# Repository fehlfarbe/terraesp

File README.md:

# ESP32 terrarium controller

With this project you can control your terrarium's temperature, light, sprinkler and so on via webinterface.

## Features

* Reads different Sensors for temperature and humidity (DHT22, SHT3x, DS1820, ...) and analog sensors to measure soil moisture etc.
* Timers for day/night light switch
* Actions if threshold for a sensor is reached e.g. to start sprinkler for 10s if humidity is under threshold
* Webinterface:
  * 24h log of temperature and humidity, actions etc.
  * control for buttons/actors and sliders for PWM pins
  * change config
* OTA update via WiFi

## Webinterface

The webinterface has interactive controls to toggle relays or set PWM values to set the brightness of LEDs or fan speed.

A chart shows the measured temperatures (red) and humidity (blue) of your configured sensors and events (green) like time on, off and so on.

You can add sensors, actuators (relay, pwm), timers and thresholds in the 'settings' section.

## Parts needed

* ESP32 dev board
* DHT22 / SHT31 / analog temperature and humidity sensor
* Relay or SSR board to control lights/pump
* MOSFET board to control LED brightness, fan speed etc. via PWM
* WiFi connection for time sync

The device creates an access point on first start. Then you can configure your WiFi and pin settings.

## Caution

The WiFi password is saved without encryption on the device. Also OTA-update has default password "admin" at the moment. Change it if you want to secure your device for unauthorized updates.

> **Make the webinterface accessible from the internet is a very bad idea! Please use a VPN or something else to prevent a flooded terrarium ;-)**

## Installation

* Download / Clone this repository
* Install PlatformIO: <https://docs.platformio.org/en/latest/ide/pioide.html>
* Open this project in PlatformIO
* Connect your ESP32 via USB cable and upload sketch and [filesystem](https://docs.platformio.org/en/latest/platforms/espressif32.html#uploading-files-to-file-system-spiffs)
  * Run task -> Upload file system image
  * or run `pio run -t uploadfs`
  * Uploading filesystem will overwrite your settings!
* Reboot ESP32, it will create an AccessPoint with name ESP_xxxx
* Connect to the AP and open <http://192.168.4.1> in Browser
* Connect to your WiFi network
* Setup pins, sensor and so on in the webinterface

## Problems

* If PlatformIO can't find the libraries, switch to the cloned directory, open a terminal and type `pio lib install`. The command should download all necessary libraries.
* Windows users: if you get errors like `error: 'timeinfo' has incomplete type` just delete the `Time.h` header in `.pio/libdeps/{ota,usb}/Time` after installing the libs. The bug happens only on Windows because it's not case-sensitive and mixes the `time.h` header with `Time.h` of TimeLib library.

## PCB

Prototype PCB with several new features:

* 12V supply voltage for board and PWM/switches
* Directly soldered ESP32 with 12V -> 5V -> 3V3 converter
* 4x SSR to switch 230V AC with one 230V AC input and 3-4x outputs (is this safe??)
* 4x MOSFETs for PWM with supply voltage (to set the brightness of a 12V LED strip or control the speed of a fan)
* Connect multiple sensors/displays/whatever via i2c bus
* Connect analog sensors

## ToDo

* [ ] webinterface with authorization
* [ ] better instructions
* [ ] import/export config
* [x] The current hardware setup is a mess  with many jumper cables and so on. So I want to create PCB with relays/SSR, MOSFETS, power supply
* [ ] PID controller for heater/humidifier?
* [ ] PCB: switch from EAGLE to KiCAD (in progress...)
* [ ] PCB: replace the expensive 12V -> 5V step down (in progress...)

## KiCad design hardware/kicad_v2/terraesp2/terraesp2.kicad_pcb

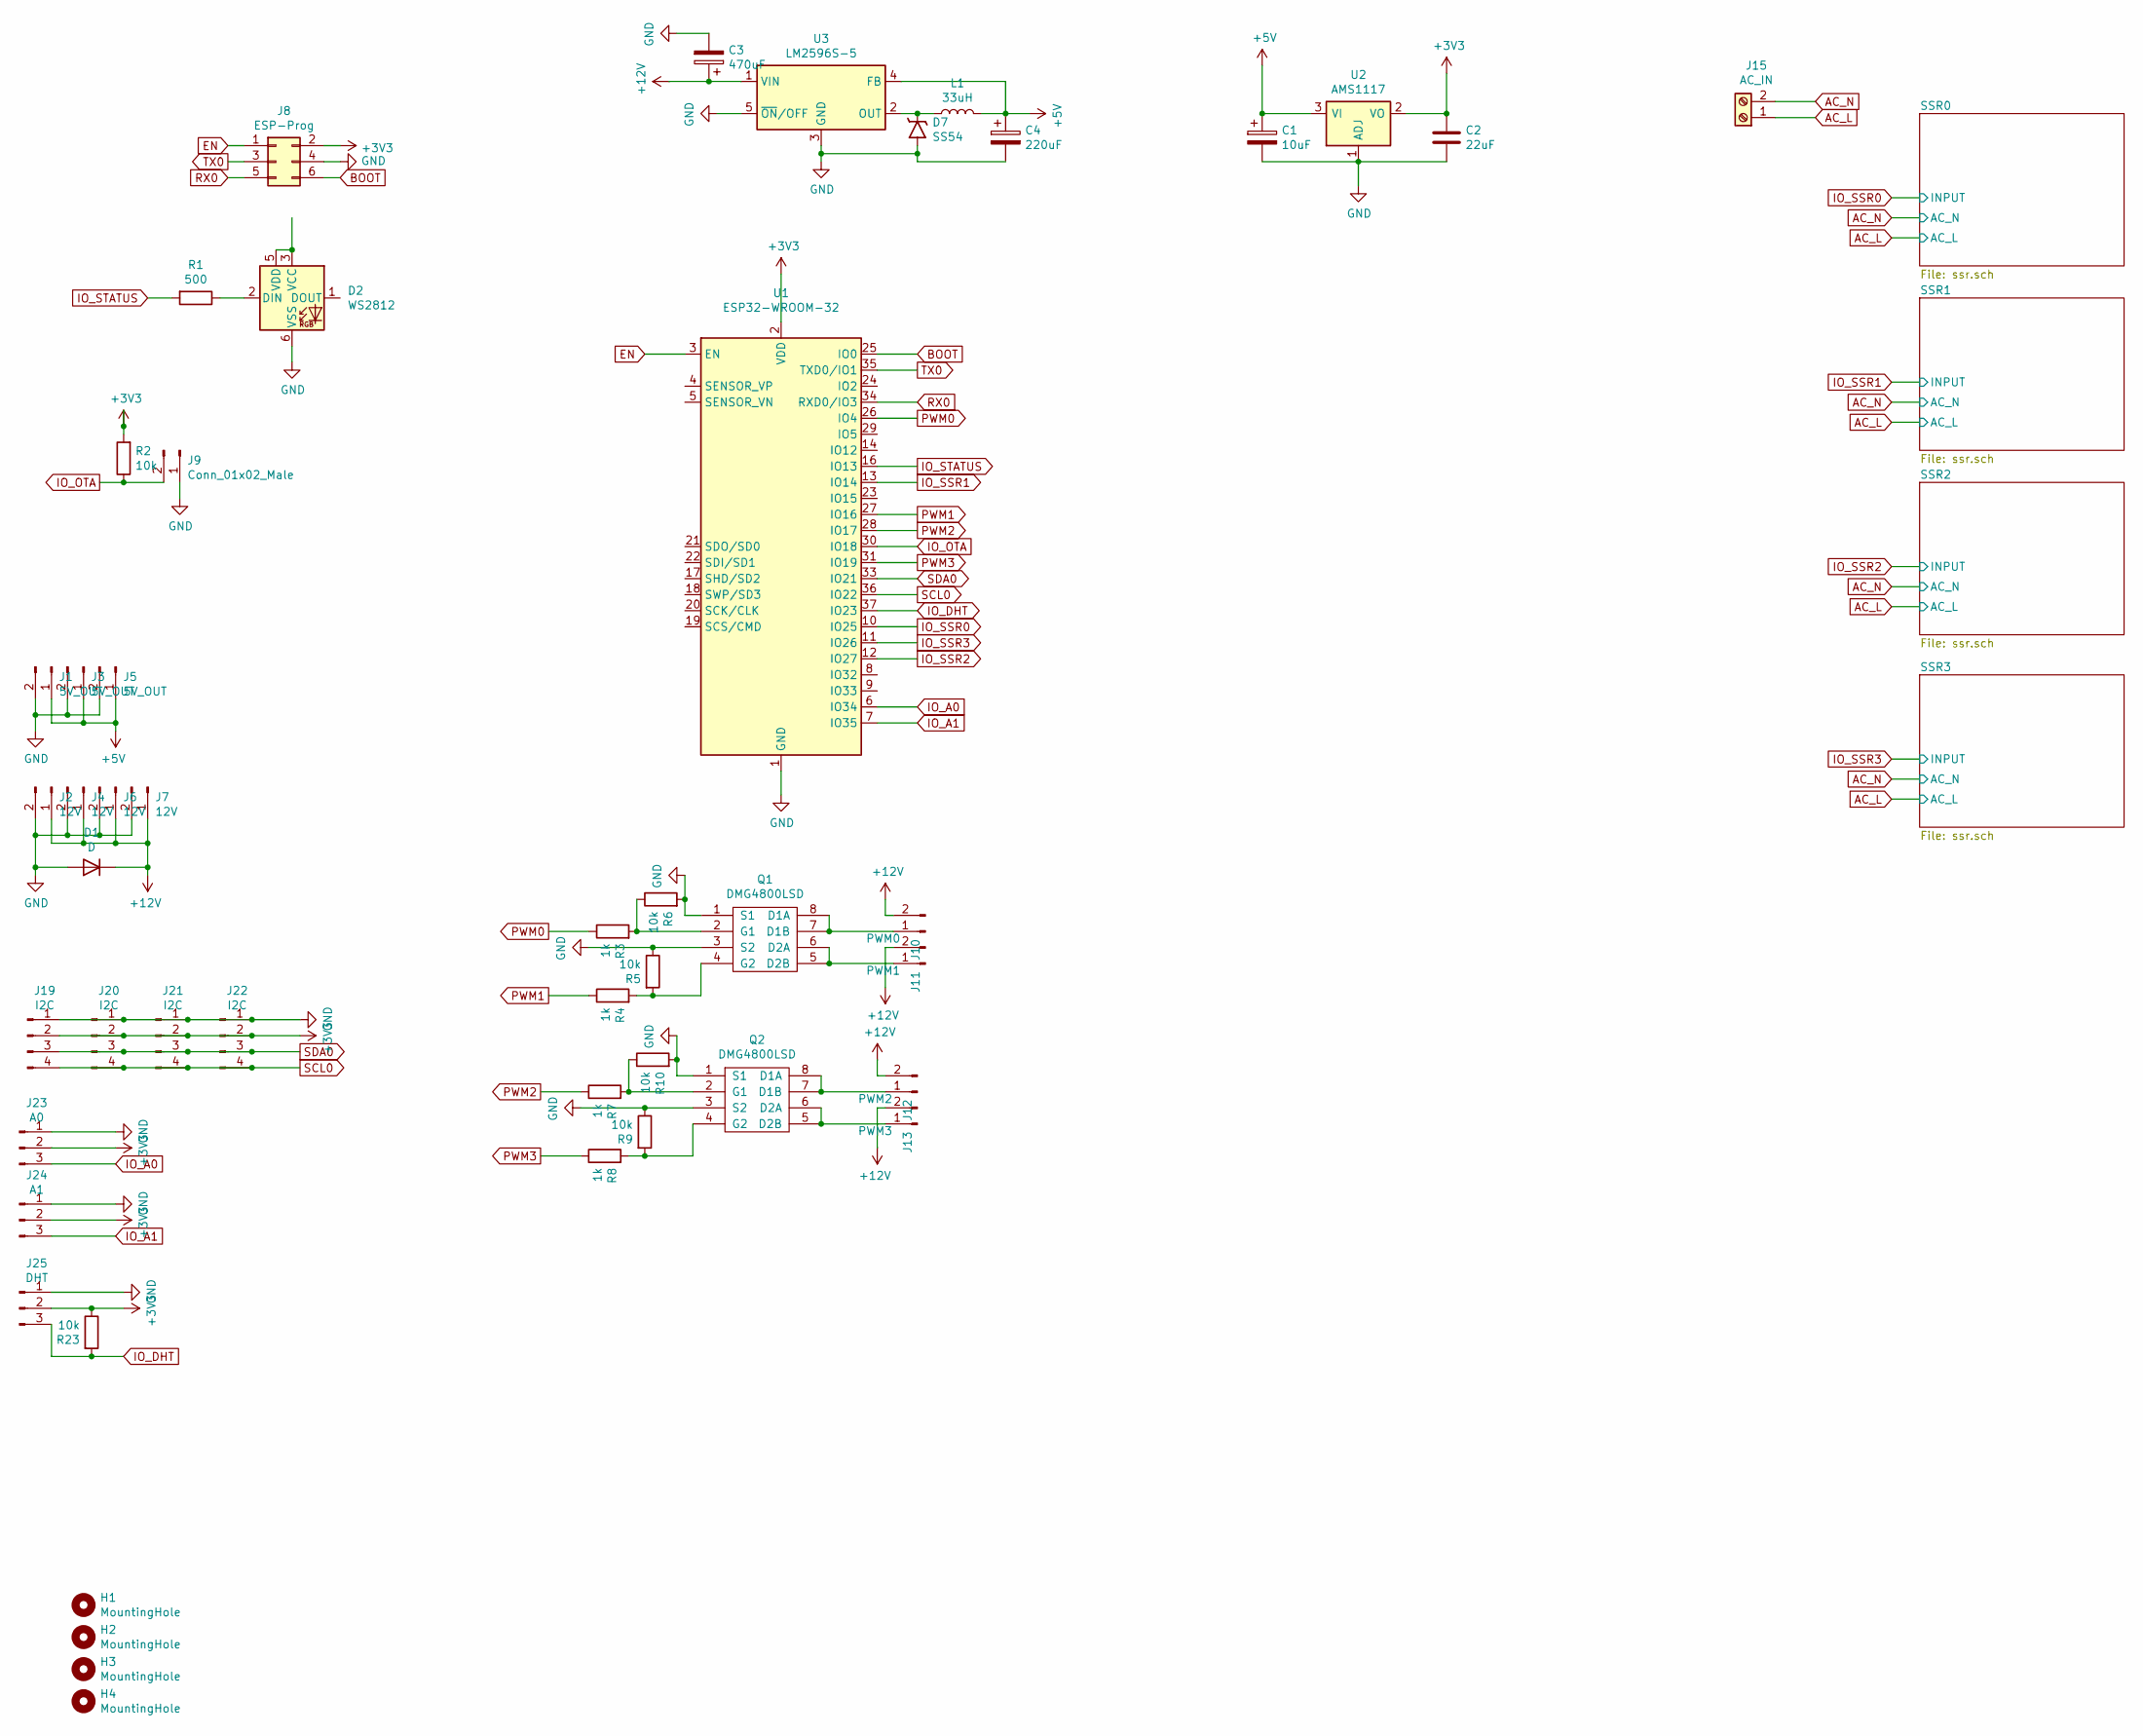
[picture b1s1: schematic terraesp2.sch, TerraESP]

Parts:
C1: 10uF; C_1206_3216Metric
C2: 22uF; CP_EIA-1608-08_AVX-J
C3: 470uF; CP_Elec_10x10.5
C4: 220uF; CP_Elec_6.3x5.8
D1: D; D_1206_3216Metric
D2: WS2812; LED_WS2812_PLCC6_5.0x5.0mm_P1.6mm
D7: SS54; DO-214AC
H1, H2, H3, H4: MountingHole; MountingHole_3.2mm_M3
J1, J3, J5: 5V_OUT; Molex_KK-254_AE-6410-02A_1x02_P2.54mm_Vertical
J2, J4, J6, J7: 12V; Molex_KK-254_AE-6410-02A_1x02_P2.54mm_Vertical
J8: ESP-Prog; IDC-Header_2x03_P2.54mm_Vertical
J9: Conn_01x02_Male; PinHeader_1x02_P2.54mm_Vertical
J10: PWM0; Molex_KK-254_AE-6410-02A_1x02_P2.54mm_Vertical
J11: PWM1; Molex_KK-254_AE-6410-02A_1x02_P2.54mm_Vertical
J12: PWM2; Molex_KK-254_AE-6410-02A_1x02_P2.54mm_Vertical
J13: PWM3; Molex_KK-254_AE-6410-02A_1x02_P2.54mm_Vertical
J15: AC_IN; TerminalBlock_Phoenix_MKDS-1,5-2_1x02_P5.00mm_Horizontal
J19, J20, J21, J22: I2C; Molex_KK-254_AE-6410-04A_1x04_P2.54mm_Vertical
J23: A0; Molex_KK-254_AE-6410-03A_1x03_P2.54mm_Vertical
J24: A1; Molex_KK-254_AE-6410-03A_1x03_P2.54mm_Vertical
J25: DHT; Molex_KK-254_AE-6410-03A_1x03_P2.54mm_Vertical
L1: 33uH; L_12x12mm_H8mm
Q1, Q2: DMG4800LSD; Diodes_Inc.-SO-8-03_2017-0-MFG
R1: 500; R_1206_3216Metric
R2, R5, R6, R9, R10, R23: 10k; R_1206_3216Metric
R3, R4, R7, R8: 1k; R_1206_3216Metric
U1: ESP32-WROOM-32
U2: AMS1117; SOT-223-3_TabPin2
U3: LM2596S-5; TO-263-5_TabPin3

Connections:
+3V3: C2.1, J8.2, J19.2, J20.2, J21.2, J22.2, J23.2, J24.2, J25.2, R2.2, R23.1, U1.2 (VDD), U2.2 (VO)
+5V: C1.1, C4.1, J1.1, J3.1, J5.1, L1.2, U2.3 (VI), U3.4 (FB); also elsewhere on the board
+12V: C3.1, D1.1 (K), J2.1, J4.1, J6.1, J7.1, J10.2, J11.2, J12.2, J13.2, U3.1 (VIN)
AC_L: J15.1; also elsewhere on the board
AC_N: J15.2; also elsewhere on the board
BOOT: J8.6, U1.25 (IO0)
EN: J8.1, U1.3 (EN)
GND: C1.2, C2.2, C3.2, C4.2, D1.2 (A), D2.6 (VSS), D7.A, J1.2, J2.2, J3.2, J4.2, J5.2, J6.2, J7.2, J8.4, J9.1, J19.1, J20.1, J21.1, J22.1, J23.1, J24.1, J25.1, Q1.1 (S1), Q1.3 (S2), Q2.1 (S1), Q2.3 (S2), R5.1, R6.2, R9.1, R10.2, U1.1 (GND), U1.15 (GND), U1.38 (GND), U1.39 (GND), U2.1 (ADJ), U3.3 (GND), U3.5 (~ON~/OFF); also elsewhere on the board
IO_A0: J23.3, U1.6 (IO34)
IO_A1: J24.3, U1.7 (IO35)
IO_DHT: J25.3, R23.2, U1.37 (IO23)
IO_OTA: J9.2, R2.1, U1.30 (IO18)
IO_SSR0: U1.10 (IO25); also elsewhere on the board
IO_SSR1: U1.13 (IO14); also elsewhere on the board
IO_SSR2: U1.12 (IO27); also elsewhere on the board
IO_SSR3: U1.11 (IO26); also elsewhere on the board
IO_STATUS: R1.2, U1.16 (IO13)
unnamed: D2.2 (DIN), R1.1
unnamed: D2.3 (VCC), D2.5 (VDD)
unnamed: D7.C, L1.1, U3.2 (OUT)
unnamed: J10.1, Q1.7 (D1B), Q1.8 (D1A)
unnamed: J11.1, Q1.5 (D2B), Q1.6 (D2A)
unnamed: J12.1, Q2.7 (D1B), Q2.8 (D1A)
unnamed: J13.1, Q2.5 (D2B), Q2.6 (D2A)
unnamed: Q1.2 (G1), R3.2, R6.1
unnamed: Q1.4 (G2), R4.2, R5.2
unnamed: Q2.2 (G1), R7.2, R10.1
unnamed: Q2.4 (G2), R8.2, R9.2
PWM0: R3.1, U1.26 (IO4)
PWM1: R4.1, U1.27 (IO16)
PWM2: R7.1, U1.28 (IO17)
PWM3: R8.1, U1.31 (IO19)
RX0: J8.5, U1.34 (RXD0/IO3)
SCL0: J19.4, J20.4, J21.4, J22.4, U1.36 (IO22)
SDA0: J19.3, J20.3, J21.3, J22.3, U1.33 (IO21)
TX0: J8.3, U1.35 (TXD0/IO1)

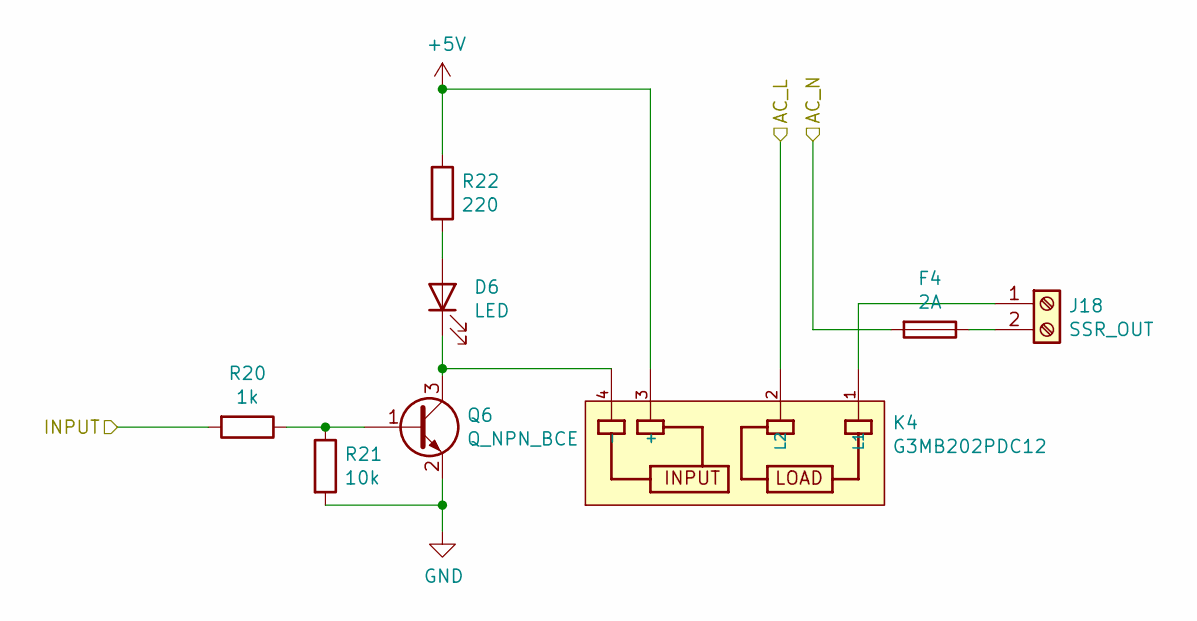
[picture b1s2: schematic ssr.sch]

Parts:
D3: LED; LED_1206_3216Metric
F1: 2A; ASI PTF-76 5x20mm Fuse Holder
J14: SSR_OUT; TerminalBlock_Phoenix_MKDS-1,5-2_1x02_P5.00mm_Horizontal
K1: G3MB202PDC12; RELAY_G3MB202PDC12; PARTREV N/A
Q3: Q_NPN_BCE; SOT-23
R11: 1k; R_1206_3216Metric
R12: 10k; R_1206_3216Metric
R13: 220; R_1206_3216Metric

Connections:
+5V: K1.3 (+), R13.1; also elsewhere on the board
AC_L: K1.2 (L2); also elsewhere on the board
AC_N: F1.2; also elsewhere on the board
GND: Q3.2 (E), R12.2; also elsewhere on the board
IO_SSR0: R11.2; also elsewhere on the board
unnamed: D3.1 (K), K1.4 (-), Q3.3 (C)
unnamed: D3.2 (A), R13.2
unnamed: F1.1, J14.2
unnamed: J14.1, K1.1 (L1)
unnamed: Q3.1 (B), R11.1, R12.1

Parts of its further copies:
D4, D5, D6: LED; LED_1206_3216Metric
F2, F3, F4: 2A; ASI PTF-76 5x20mm Fuse Holder
J16, J17, J18: SSR_OUT; TerminalBlock_Phoenix_MKDS-1,5-2_1x02_P5.00mm_Horizontal
K2, K3, K4: G3MB202PDC12; RELAY_G3MB202PDC12; PARTREV N/A
Q4, Q5, Q6: Q_NPN_BCE; SOT-23
R14, R17, R20: 1k; R_1206_3216Metric
R15, R18, R21: 10k; R_1206_3216Metric
R16, R19, R22: 220; R_1206_3216Metric

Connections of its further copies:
+5V: K2.3 (+), K3.3 (+), K4.3 (+), R16.1, R19.1, R22.1; also elsewhere on the board
AC_L: K2.2 (L2), K3.2 (L2), K4.2 (L2); also elsewhere on the board
AC_N: F2.2, F3.2, F4.2; also elsewhere on the board
GND: Q4.2 (E), Q5.2 (E), Q6.2 (E), R15.2, R18.2, R21.2; also elsewhere on the board
IO_SSR1: R14.2; also elsewhere on the board
IO_SSR2: R17.2; also elsewhere on the board
IO_SSR3: R20.2; also elsewhere on the board
unnamed: D4.1 (K), K2.4 (-), Q4.3 (C)
unnamed: D4.2 (A), R16.2
unnamed: D5.1 (K), K3.4 (-), Q5.3 (C)
unnamed: D5.2 (A), R19.2
unnamed: D6.1 (K), K4.4 (-), Q6.3 (C)
unnamed: D6.2 (A), R22.2
unnamed: F2.1, J16.2
unnamed: F3.1, J17.2
unnamed: F4.1, J18.2
unnamed: J16.1, K2.1 (L1)
unnamed: J17.1, K3.1 (L1)
unnamed: J18.1, K4.1 (L1)
unnamed: Q4.1 (B), R14.1, R15.1
unnamed: Q5.1 (B), R17.1, R18.1
unnamed: Q6.1 (B), R20.1, R21.1

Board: 2 copper layers, 81 parts (0 on the bottom side), 56 nets, no tracks yet.

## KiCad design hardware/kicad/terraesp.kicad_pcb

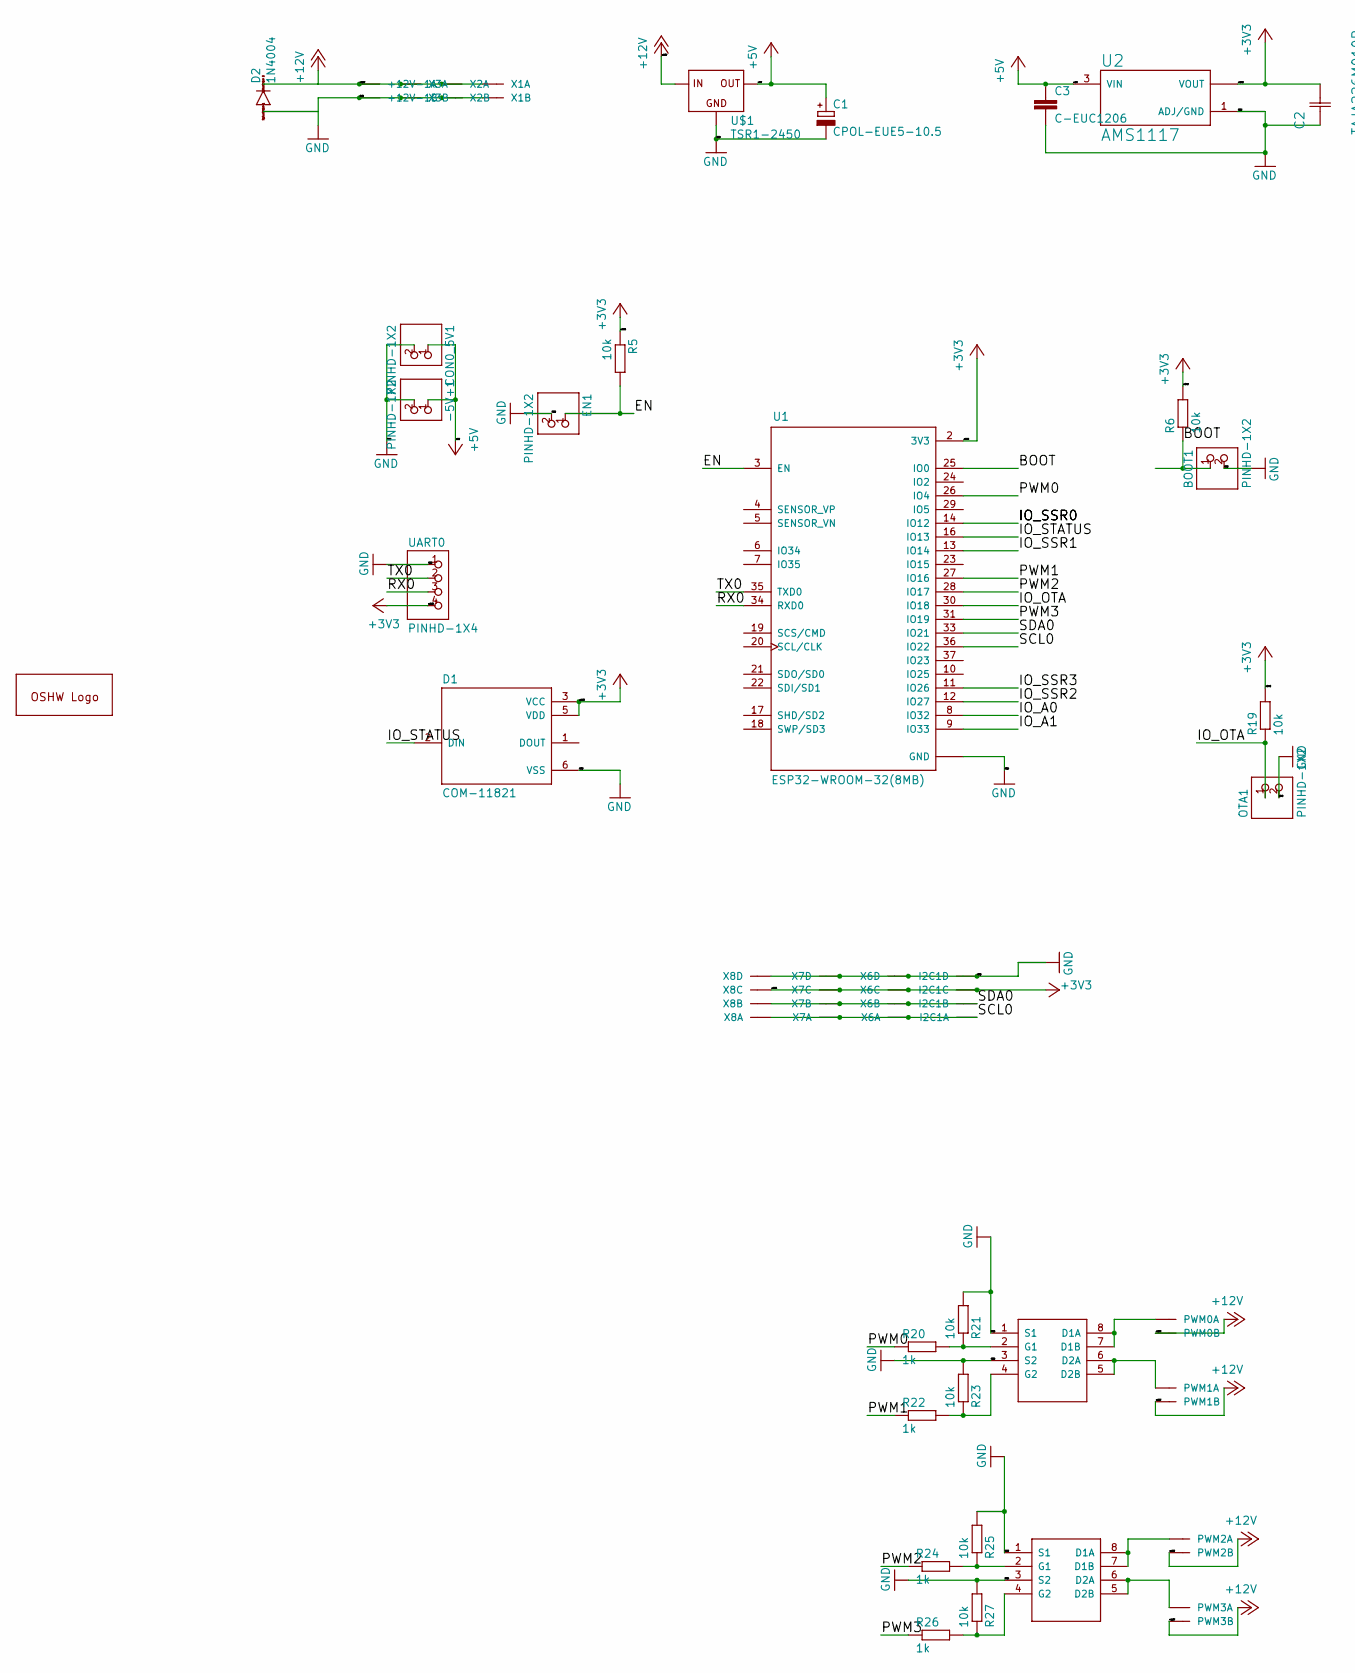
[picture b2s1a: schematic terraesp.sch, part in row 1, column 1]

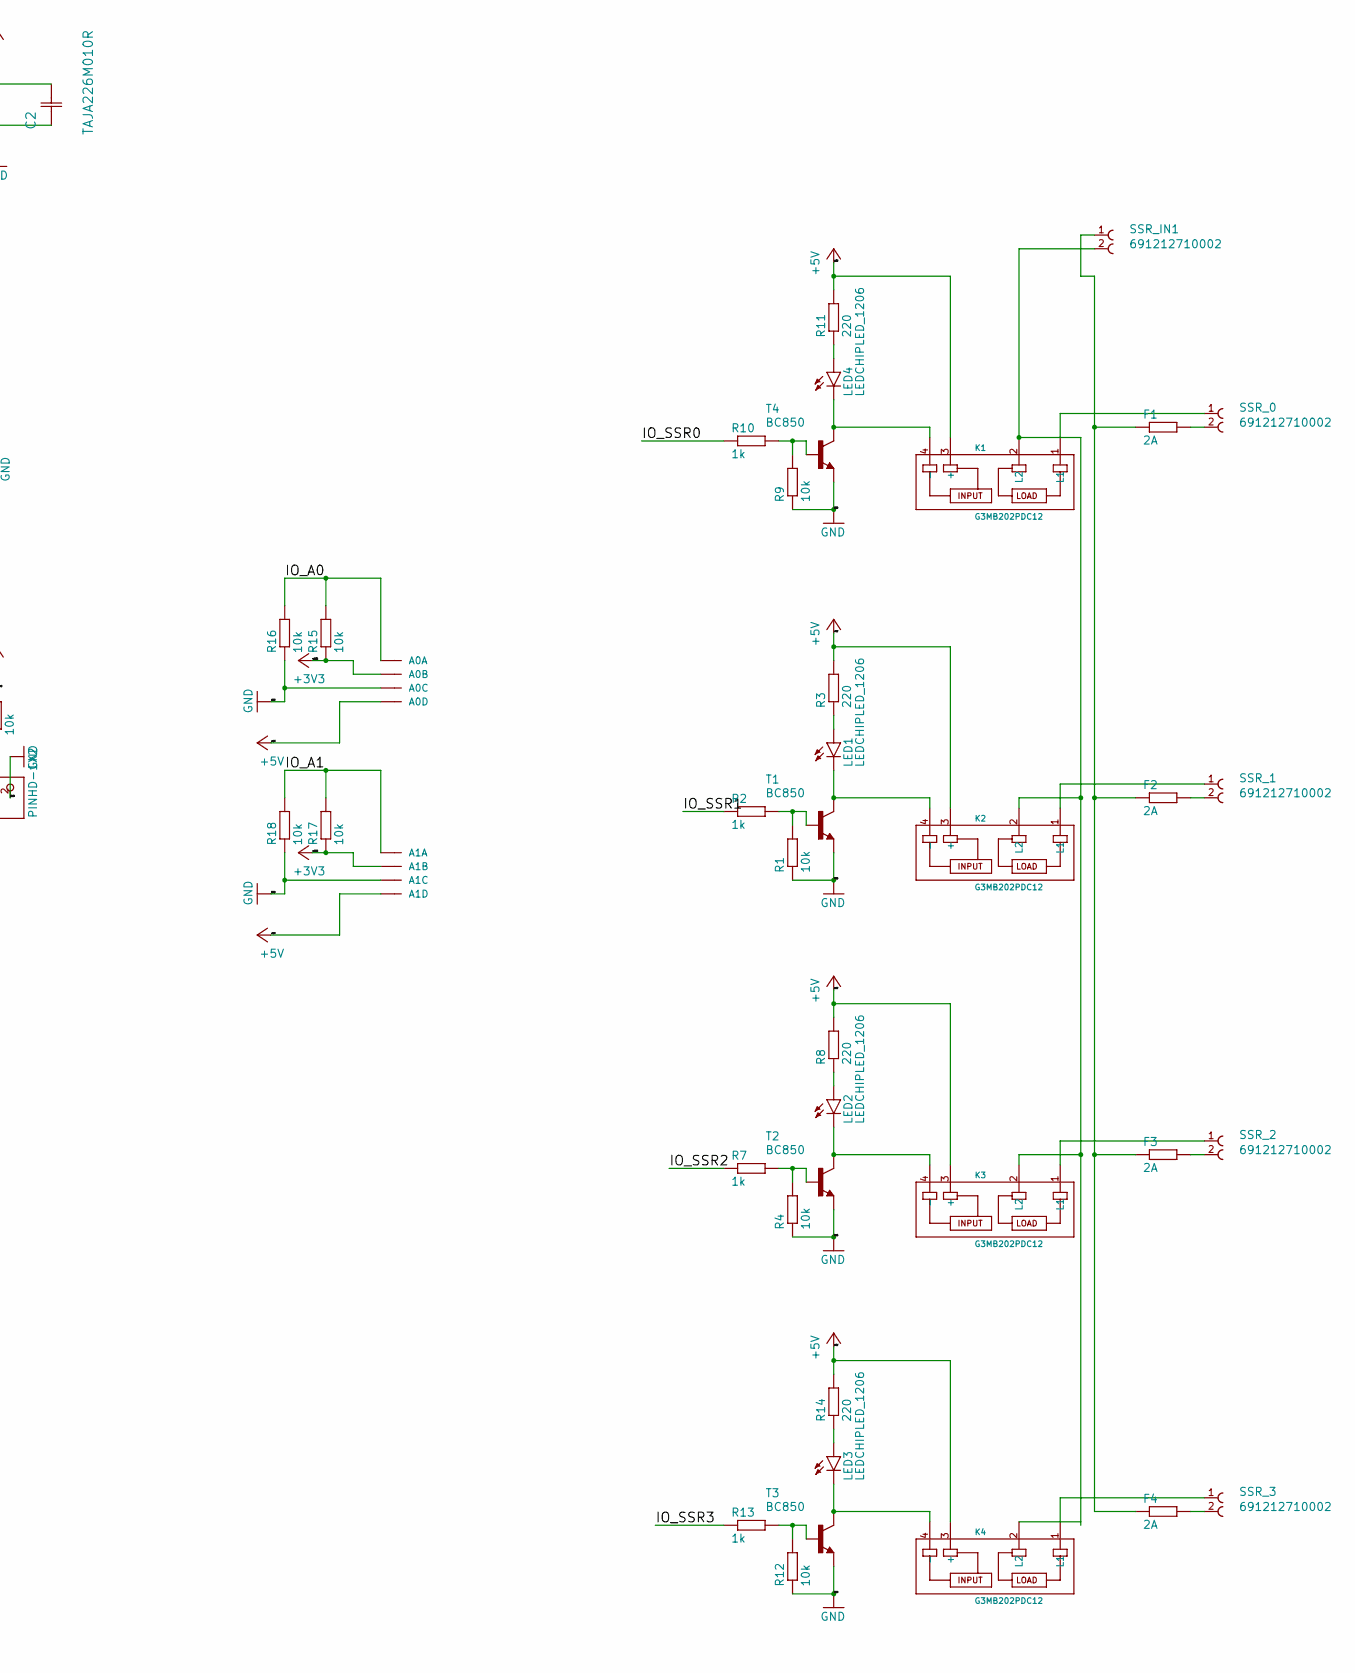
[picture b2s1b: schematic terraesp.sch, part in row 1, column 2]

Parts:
+12V-1: 22-23-2021
-5V+1: PINHD-1X2; 1X02
A0, A1: 22-23-2041
BOOT1: PINHD-1X2; 1X02
C1: CPOL-EUE5-10.5; E5-10,5
C2: TAJA226M010R; CAPCP3216X180N
C3: C-EUC1206; C1206
CON0_5V1: PINHD-1X2; 1X02
D1: COM-11821; LED_COM-11821
D2: 1N4004; DO41-10
EN1: PINHD-1X2; 1X02
F1, F2, F3, F4: 2A; 0207_10
GOLD_ORB_SM2: OSHWLOGOLOGO5MM; OSHW_5MM
I2C1: 22-23-2041
K1, K2, K3, K4: G3MB202PDC12; RELAY_G3MB202PDC12
LED1, LED2, LED3, LED4: LEDCHIPLED_1206; CHIPLED_1206
OTA1: PINHD-1X2; 1X02
PWM0, PWM1, PWM2, PWM3: 22-23-2021
R1, R4, R9, R12: 10k; R1206
R2, R7, R10, R13, R20, R22, R24, R26: 1k; R1206
R3, R8, R11, R14: 220; R1206
R5, R6, R15, R16, R17, R18, R19, R21, R23, R25, R27: 10k; M1206
SSR_0, SSR_1, SSR_2, SSR_3: 691212710002
SSR_IN1: 691212710002
T1, T2, T3, T4: BC850; SOT23
U1: ESP32-WROOM-32(8MB); MODULE_ESP32-WROOM-32(8MB)
U2: AMS1117; SOT229P700X180-4N
U$1: TSR1-2450
U$2, U$3: DMG4800LSD; SOIC127P600X144-8
UART0: PINHD-1X4; 1X04
X1, X2, X3: 22-23-2021
X6, X7, X8: 22-23-2041

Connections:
+3V3: A0.2, A1.2, C2.2 (C2), D1.3 (VCC), D1.5 (VDD), I2C1.3, R5.1, R6.2, R15.1, R17.1, R19.2, U1.2 (3V3), U2.2 (VOUT), U2.4 (VOUT), UART0.4, X6.3, X7.3, X8.3
+5V: -5V+1.1, A0.4, A1.4, C1.+, C3.1, CON0_5V1.1, K1.3 (+), K2.3 (+), K3.3 (+), K4.3 (+), R3.2, R8.2, R11.2, R14.2, U2.3 (VIN), U$1.3 (OUT)
+12V: +12V-1.1, D2.C, PWM0.2, PWM1.2, PWM2.2, PWM3.2, U$1.1 (IN), X1.1, X2.1, X3.1
/BOOT: BOOT1.1, R6.1, U1.25 (IO0)
/EN: EN1.1, R5.2, U1.3 (EN)
/IO_A0: A0.1, R15.2, R16.2, U1.8 (IO32)
/IO_A1: A1.1, R17.2, R18.2, U1.9 (IO33)
/IO_OTA: OTA1.1, R19.1, U1.30 (IO18)
/IO_SSR0: R10.1, U1.14 (IO12)
/IO_SSR1: R2.1, U1.13 (IO14)
/IO_SSR2: R7.1, U1.12 (IO27)
/IO_SSR3: R13.1, U1.11 (IO26)
/IO_STATUS: D1.2 (DIN), U1.16 (IO13)
/PWM0: R20.1, U1.26 (IO4)
/PWM1: R22.1, U1.27 (IO16)
/PWM2: R24.1, U1.28 (IO17)
/PWM3: R26.1, U1.31 (IO19)
/RX0: U1.34 (RXD0), UART0.3
/SCL0: I2C1.1, U1.36 (IO22), X6.1, X7.1, X8.1
/SDA0: I2C1.2, U1.33 (IO21), X6.2, X7.2, X8.2
/TX0: U1.35 (TXD0), UART0.2
GND: +12V-1.2, -5V+1.2, A0.3, A1.3, BOOT1.2, C1.-, C2.1 (C1), C3.2, CON0_5V1.2, D1.6 (VSS), EN1.2, I2C1.4, OTA1.2, R1.1, R4.1, R9.1, R12.1, R16.1, R18.1, R21.2, R23.2, R25.2, R27.2, T1.2 (E), T2.2 (E), T3.2 (E), T4.2 (E), U1.1 (GND), U1.15 (GND), U1.38 (GND), U1.39 (GND), U2.1 (ADJ/GND), U$1.2 (GND), U$2.1 (S1), U$2.3 (S2), U$3.1 (S1), U$3.3 (S2), UART0.1, X1.2, X2.2, X3.2, X6.4, X7.4, X8.4
unnamed: F1.1, F2.1, F3.1, F4.1, SSR_IN1.1
unnamed: F1.2, SSR_0.2
unnamed: F2.2, SSR_1.2
unnamed: F3.2, SSR_2.2
unnamed: F4.2, SSR_3.2
unnamed: K1.1 (L1), SSR_0.1
unnamed: K1.2 (L2), K2.2 (L2), K3.2 (L2), K4.2 (L2), SSR_IN1.2
unnamed: K1.4 (-), LED4.C, T4.3 (C)
unnamed: K2.1 (L1), SSR_1.1
unnamed: K2.4 (-), LED1.C, T1.3 (C)
unnamed: K3.1 (L1), SSR_2.1
unnamed: K3.4 (-), LED2.C, T2.3 (C)
unnamed: K4.1 (L1), SSR_3.1
unnamed: K4.4 (-), LED3.C, T3.3 (C)
unnamed: LED1.A, R3.1
unnamed: LED2.A, R8.1
unnamed: LED3.A, R14.1
unnamed: LED4.A, R11.1
unnamed: PWM0.1, U$2.7 (D1B), U$2.8 (D1A)
unnamed: PWM1.1, U$2.5 (D2B), U$2.6 (D2A)
unnamed: PWM2.1, U$3.7 (D1B), U$3.8 (D1A)
unnamed: PWM3.1, U$3.5 (D2B), U$3.6 (D2A)
unnamed: R1.2, R2.2, T1.1 (B)
unnamed: R4.2, R7.2, T2.1 (B)
unnamed: R9.2, R10.2, T4.1 (B)
unnamed: R12.2, R13.2, T3.1 (B)
unnamed: R20.2, R21.1, U$2.2 (G1)
unnamed: R22.2, R23.1, U$2.4 (G2)
unnamed: R24.2, R25.1, U$3.2 (G1)
unnamed: R26.2, R27.1, U$3.4 (G2)

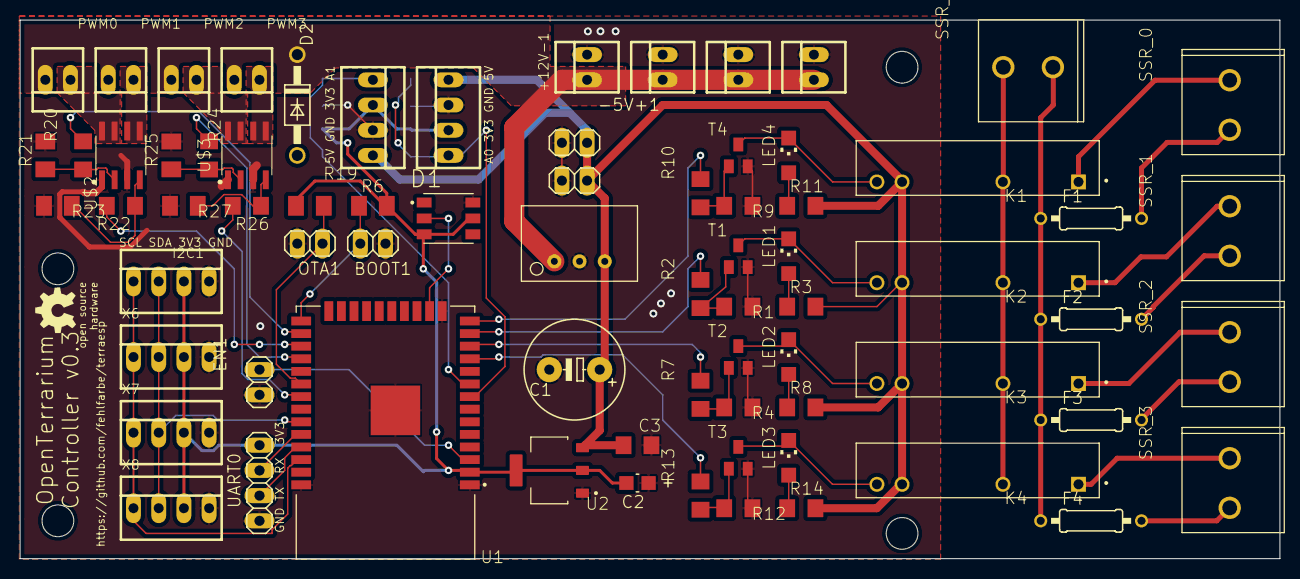
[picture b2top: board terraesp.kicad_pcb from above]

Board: 2 copper layers, 127.0 x 54.3 mm, 83 parts (0 on the bottom side), 52 nets.

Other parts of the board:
@HOLE0, @HOLE1, @HOLE2, @HOLE3: (no value)

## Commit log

2017-10-29 Cleanup
2018-01-03 Added OTA update Device creates Access Point if WiFi network is not reachable (for first config) Fixed some time sync issues Added multiple retries for DHT sensor readout (there are many communicatio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
2018-01-04 Added alternativ DHT library
2018-01-07 Added Serial/Telnet debug output
2018-01-08 Added Serial/Telnet debug output Modified upload.sh - doesn't overwrite config.json on device js librarys are stored local on the device (so internet access is only needed for time update) Some minor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
2018-01-14 Minor fixes
2018-01-21 Added new config menu
2018-01-21 Added some documentation
2019-02-02 converted to platformio
2019-02-10 Changed to platformio project WiFi password is no longer visible on config page
2019-02-10 restructured project
2019-02-12 not working yet
2019-06-09 Added WifiManager, updated platformio.ini and README
2019-09-10 Added new sensors
2019-09-16 Different sensors are working now Reading sensors from config file
2019-09-16 Added prototype PCB layout
2019-10-05 Updated to ArduinoJSON6 Updated Webinterface Compressed CSS/JS files
2019-10-06 Added new classes for Threshold and Timer buttons, sensors, timers, thresholds should work now
2019-10-06 Added threshold lines to web chart
2019-10-08 Added events (button toggle, timer, threshold reached) Bugfixes
2019-11-07 New sensors Switched to AngularJS SPA (in progress...)
2020-09-24 new webinterface
2020-12-06 - Many bugfixes - Webinterface is working - create_www.sh bundles all dependencies in one lib (webinterface loads much faster, no exceptions because of too many parallel streams anymore)
2021-01-18 Bugfixes for analog sensor and PWM actuator
2021-01-30 Switched from chart.js to flot.js Several bugfixes Removed TimeAlarms lib and made own timer Added bootstrap toggle for webinterface
2021-01-30 Several bugfixes Removed TimeAlarms lib and made own timer Added bootstrap toggle for webinterface
2021-01-30 Create LICENSE
2021-01-30 Updated README.md Deleted old Fritzing PCB Converted EAGLE project to KiCAD (not tested yet!)
2021-02-20 Updated README Created KiCAD PCB (in progress)
2021-02-21 Fixed Time.h conflict on Windows
2021-02-22 Fixed some TimeLib related includes and added note to README for Windows users
2021-03-06 Updated README and removed www update on filesystem upload
2021-03-06 Added mklittlefs.exe for Windows
2021-03-27 Switched back to Adafruit lib for DHT sensors
2021-12-21 removed DHT sensor for #4
2021-12-21 removed old DHT sensor lib
2022-06-20 Refactoring
2022-06-21 refactoring min/max args
2023-10-24 Updated platformio.ini and fixes #6
2026-02-01 Updated libs
2026-02-12 Updated to latest ArduinoJson 7
2026-02-12 Fixed threshold bug that immediately deactivates turned on actuators
2026-02-12 Code format
2026-02-12 Code cleanup

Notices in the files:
hardware/kicad_v2/terraesp2/terraesp2.sch:
License: MIT
